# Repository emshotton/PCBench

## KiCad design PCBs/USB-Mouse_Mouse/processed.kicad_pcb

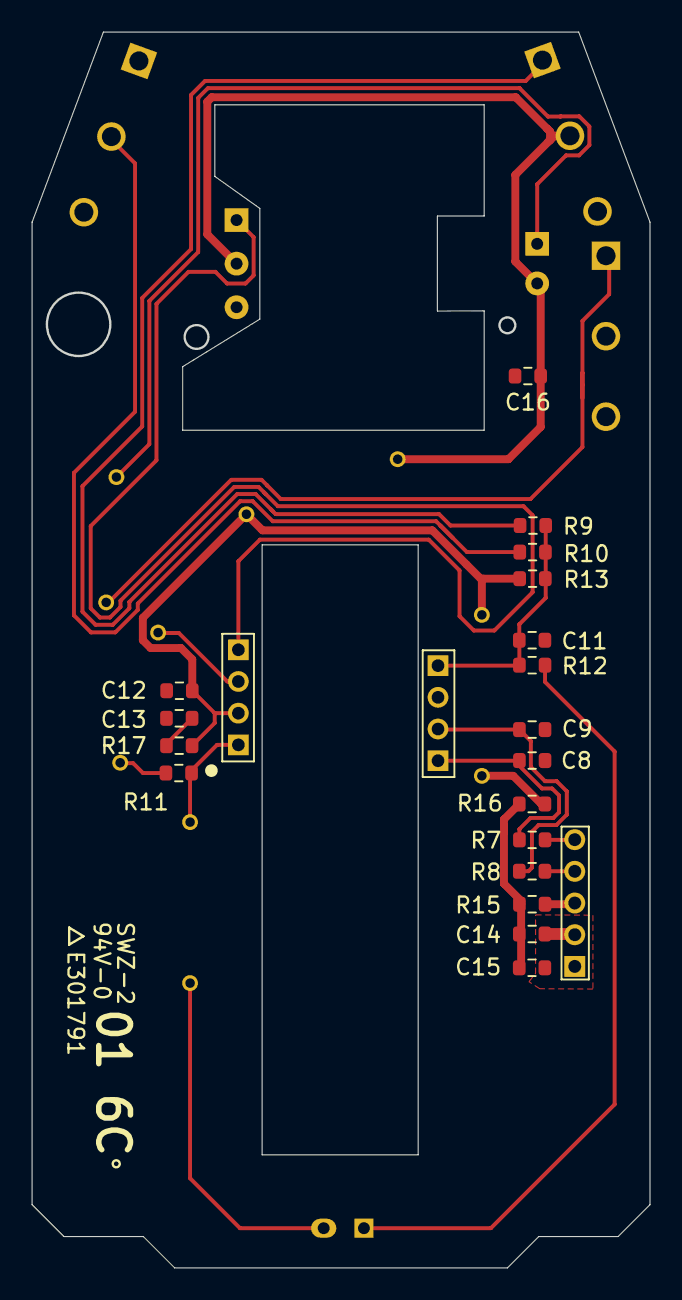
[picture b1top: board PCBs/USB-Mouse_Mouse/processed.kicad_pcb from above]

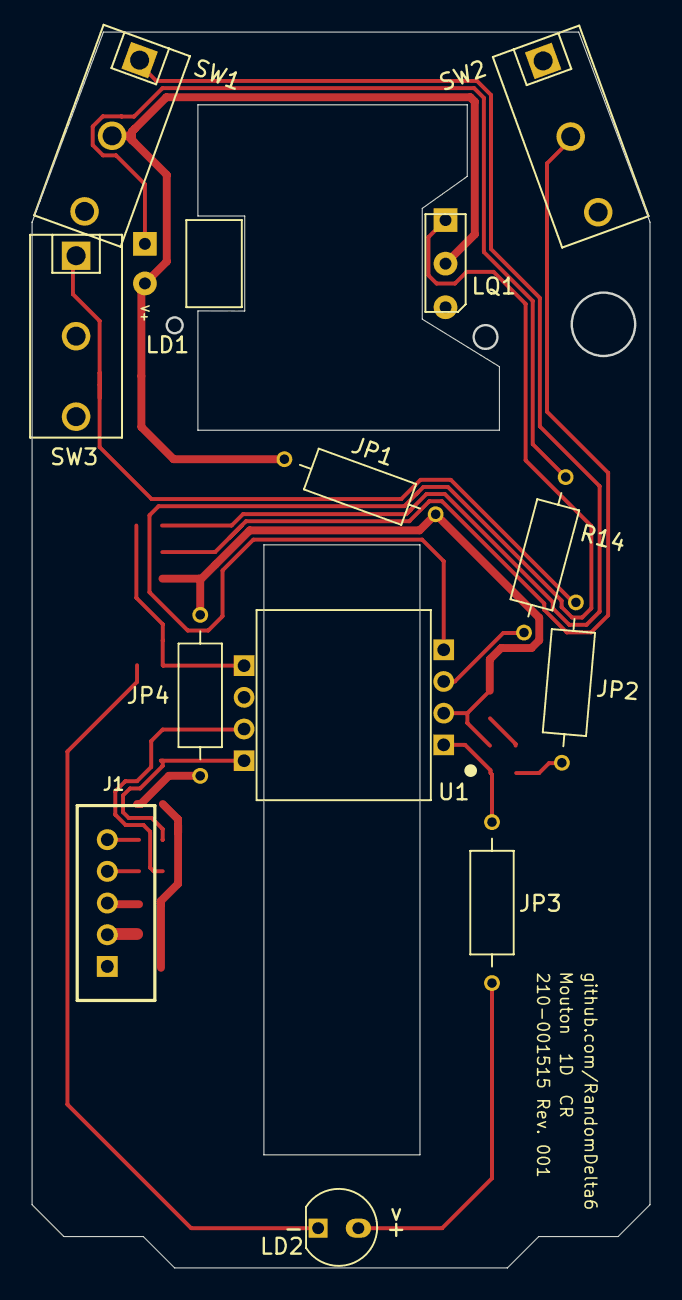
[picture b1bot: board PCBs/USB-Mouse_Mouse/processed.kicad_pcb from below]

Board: 2 copper layers, 39.0 x 78.0 mm, 31 parts (13 on the bottom side), 22 nets.

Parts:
C8, C9: C 0.01uF; R_0603_1608_Logi
C11, C13, C16: C NC; R_0603_1608_Logi
C12, C15: C 0.1uF; R_0603_1608_Logi
C14: C 4.7uF; R_0603_1608_Logi
J1: Conn_01x05_Male; JST_Conn
JP1, JP2, JP3, JP4: R; JP_Axial_DIN0207_L6.3mm_D2.5mm_P10.16mm_Horizontal
LD1: Rotary illumintion; Rot_LED
LD2: Sensor illumination; LED_Sensor
LQ1: EL; LQ1
R7, R8: R 270; R_0603_1608_Logi
R9, R10, R11: R 303; R_0603_1608_Logi
R12: R 330; R_0603_1608_Logi
R13: R 105; R_0603_1608_Logi
R14: R 1500ohm ± 5%; JP_Axial_DIN0207_L6.3mm_D2.5mm_P10.16mm_Horizontal
R15: R 1R0; R_0603_1608_Logi
R16: R 000; R_0603_1608_Logi
R17: R NC; R_0603_1608_Logi
SW1: Left click; SPDT_Switch
SW2: Right Click; SPDT_Switch
SW3: Middle click; SPDT_Switch
U1: Optical_Sensor; Sensor

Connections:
D+: C9.1, R8.2, U1.7
D-: C8.1, R7.1, U1.8
GNDREF: C8.2, C9.2, C11.1, C12.1, C13.1, C14.1, C15.2, C16.2, J1.1, J1.2, LQ1.3, SW2.1, SW3.2, U1.6
unnamed: C13.2, R17.1
unnamed: C14.2, C15.1, R15.1, R16.2
unnamed: J1.4, R8.1
unnamed: J1.5, R7.2
unnamed: JP2.1, SW3.1
unnamed: JP2.2, R11.2
unnamed: JP3.1, LD2.1
unnamed: JP4.1, R16.1
unnamed: LD1.1, R14.1
unnamed: LD2.2, R12.2
unnamed: R9.2, SW1.1
unnamed: R10.1, SW2.2
Pin_1: JP3.2, R11.1, U1.1
Pin_2: C12.2, JP1.2, JP4.2, R13.2, R17.2, U1.2
Pin_2J: C16.1, JP1.1, LD1.2, LQ1.2, SW1.2
Pin_3: R14.2, U1.3
Pin_4: LQ1.1, U1.4
Pin_5: C11.2, R9.1, R10.2, R12.1, R13.1, U1.5
VCC: J1.3, R15.2

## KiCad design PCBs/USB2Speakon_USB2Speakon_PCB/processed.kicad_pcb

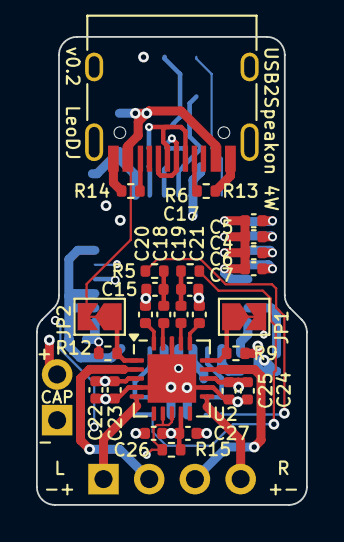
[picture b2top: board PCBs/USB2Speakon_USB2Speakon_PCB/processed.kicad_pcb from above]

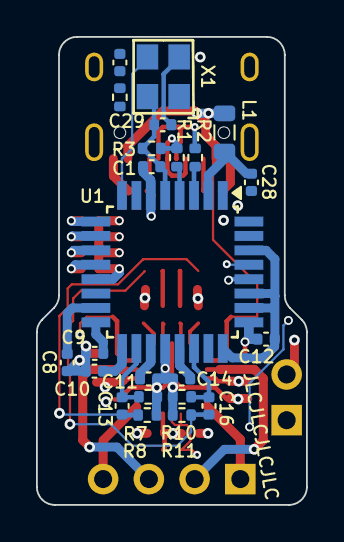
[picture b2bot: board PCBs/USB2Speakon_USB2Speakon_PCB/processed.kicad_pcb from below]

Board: 4 copper layers, 15.0 x 26.0 mm, 52 parts (23 on the bottom side), 36 nets.

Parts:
C1, C8, C11, C12, C14, C28: 1u; C_0402_1005Metric
C2: DNP; C_0402_1005Metric
C4, C5: 100p; C_0402_1005Metric
C6, C10: 3u3; C_0402_1005Metric
C7, C9, C23, C25, C27, C29: 100n; C_0402_1005Metric
C13, C16, C22, C24, C26: 10u; C_0402_1005Metric
C15, C17: 47n; C_0402_1005Metric
C18, C19, C20, C21: 470n; C_0402_1005Metric
J1: USB_C_Receptacle_USB2.0_16P; USB_C_Receptacle_HRO_TYPE-C-31-M-12
J2: Conn_01x04; PinHeader_1x04_P2.54mm_Vertical
J3: Ext_Cap; PinSocket_1x02_P2.54mm_Vertical
JP1: G0; SolderJumper-2_P1.3mm_Open_TrianglePad1.0x1.5mm
JP2: G1; SolderJumper-2_P1.3mm_Open_TrianglePad1.0x1.5mm
L1: 1uH / <0.6Ω; L_0805_2012Metric
R1, R2: 22; R_0402_1005Metric
R3: 1k5; R_0402_1005Metric
R4: DNP; R_0402_1005Metric
R5, R6: 100; R_0402_1005Metric
R7, R8, R9, R10, R11, R12, R15: 33k; R_0402_1005Metric
R13, R14: 5k1; R_0402_1005Metric
U1: PCM2912A; TQFP-32_7x7mm_P0.8mm
U2: TPA2012D2RTJR; QFN-20-1EP_4x4mm_P0.5mm_EP2.7x2.7mm
X1: 6MHz XO; OSC-SMD_4P-L3.2-W2.5-BL

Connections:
+3V3: C1.2, C29.2, R3.2, U1.5 (VDD), X1.4 (V+)
GND: C1.1, C4.1, C5.1, C6.1, C7.1, C8.1, C9.1, C10.1, C11.1, C12.1, C14.1, C15.2, C17.2, C20.2, C21.2, C22.2, C23.2, C24.2, C25.2, C26.2, C27.2, C28.2, C29.1, J1.A1 (GND), J1.A12 (GND), J1.B1 (GND), J1.B12 (GND), J1.S1 (SHIELD), J3.1, R7.2, R8.2, R9.2, R10.1, R11.1, R12.2, R13.2, R14.2, U1.1 (BGND), U1.6 (DGND), U1.13 (AGND), U1.20 (HGND), U1.23 (MAMP), U1.25 (PGND), U1.28 (TEST0), U2.4 (PGND), U2.12 (PGND), U2.18 (AGND), U2.21 (EP), X1.2 (GND)
LINE_L: C13.1, R5.1, R8.1
LINE_R: C16.1, R6.1, R11.2
unnamed: C15.1, C18.1, R5.2
unnamed: C17.1, C19.1, R6.2
unnamed: J1.A5 (CC1), R13.1
unnamed: J1.B5 (CC2), R14.1
unnamed: J1.A6 (D+), J1.B6 (D+), R1.1, R3.1
unnamed: J1.A7 (D-), J1.B7 (D-), R2.2
unnamed: J2.1, U2.5 (OUTL-)
unnamed: J2.2, U2.2 (OUTL+)
unnamed: J2.3, U2.14 (OUTR+)
unnamed: J2.4, U2.11 (OUTR-)
unnamed: R1.2, U1.4 (D+)
unnamed: R2.1, U1.3 (D-)
unnamed: C5.2, U1.9 (FL)
unnamed: C4.2, U1.10 (FR)
unnamed: C10.2, U1.17 (MBIAS)
unnamed: C28.1, L1.2, U1.2 (VBUS)
unnamed: C8.2, U1.15 (VCCCA)
unnamed: C11.2, U1.19 (VCCL)
unnamed: C14.2, U1.21 (VCCR)
unnamed: C6.2, U1.11 (VCOM1)
unnamed: C7.2, U1.12 (VCOM2)
unnamed: C9.2, U1.16 (VIN)
unnamed: C13.2, R7.1, U1.18 (VOUTL)
unnamed: C16.2, R10.2, U1.22 (VOUTR)
unnamed: U1.8 (XTI), X1.3 (OUT)
unnamed: C20.1, U2.20 (INL+)
unnamed: C18.2, U2.19 (INL-)
unnamed: C21.1, U2.16 (INR+)
unnamed: C19.2, U2.17 (INR-)
VBUS: C22.1, C23.1, C24.1, C25.1, C26.1, C27.1, J1.A4 (VBUS), J1.A9 (VBUS), J1.B4 (VBUS), J1.B9 (VBUS), J3.2, JP1.1 (A), JP1.2 (B), JP2.1 (A), JP2.2 (B), L1.1, R9.1, R12.1, R15.1, U2.1 (G1), U2.3 (PVDD), U2.9 (AVDD), U2.13 (PVDD), U2.15 (G0)
VCCP: C12.2, U1.24 (POWER), U1.26 (VCCP), U1.27 (TEST1), U1.30 (MMUTE)
~SSPND: R15.2, U1.29 (~SSPND), U2.7 (SDL), U2.8 (SDR)

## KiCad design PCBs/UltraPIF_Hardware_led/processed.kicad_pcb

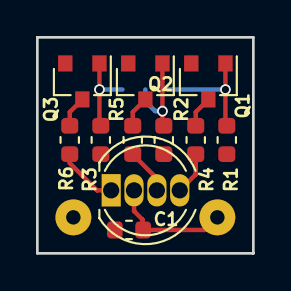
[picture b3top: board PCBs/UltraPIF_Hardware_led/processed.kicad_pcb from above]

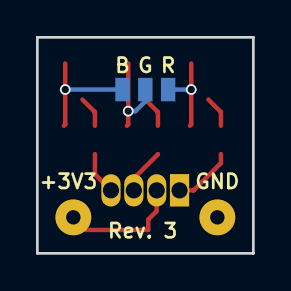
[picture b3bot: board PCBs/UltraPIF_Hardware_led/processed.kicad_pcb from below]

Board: 2 copper layers, 12.0 x 12.0 mm, 16 parts (3 on the bottom side), 11 nets.

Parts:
C1: 1u; C_0603_1608Metric
J1, J2, J3: CONN_01X01; SolderWirePad_1x01_SMD_0.8x1.3mm
J4, J5: CONN_01X01; SolderWirePad_1x01_Drill0.8mm
LD1: LED_RAGB; LED_D5.0mm-4_RGB
Q1, Q2, Q3: Q_NMOS_GSD; SOT-23
R1, R2, R3: 10k; R_0603_1608Metric
R4: 27; R_0603_1608Metric
R5: 56; R_0603_1608Metric
R6: 82; R_0603_1608Metric

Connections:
+3V3: C1.1, J4.1, LD1.2
/BLUE: J1.1, Q1.1, R1.1
/BLUE_D: Q1.3, R4.2
/BLUE_K: LD1.4, R4.1
/GREEN: J2.1, Q2.1, R2.1
/GREEN_D: Q2.3, R5.2
/GREEN_K: LD1.3, R5.1
/RED: J3.1, Q3.1, R3.1
/RED_D: Q3.3, R6.2
/RED_K: LD1.1, R6.1
GND: C1.2, J5.1, Q1.2, Q2.2, Q3.2, R1.2, R2.2, R3.2

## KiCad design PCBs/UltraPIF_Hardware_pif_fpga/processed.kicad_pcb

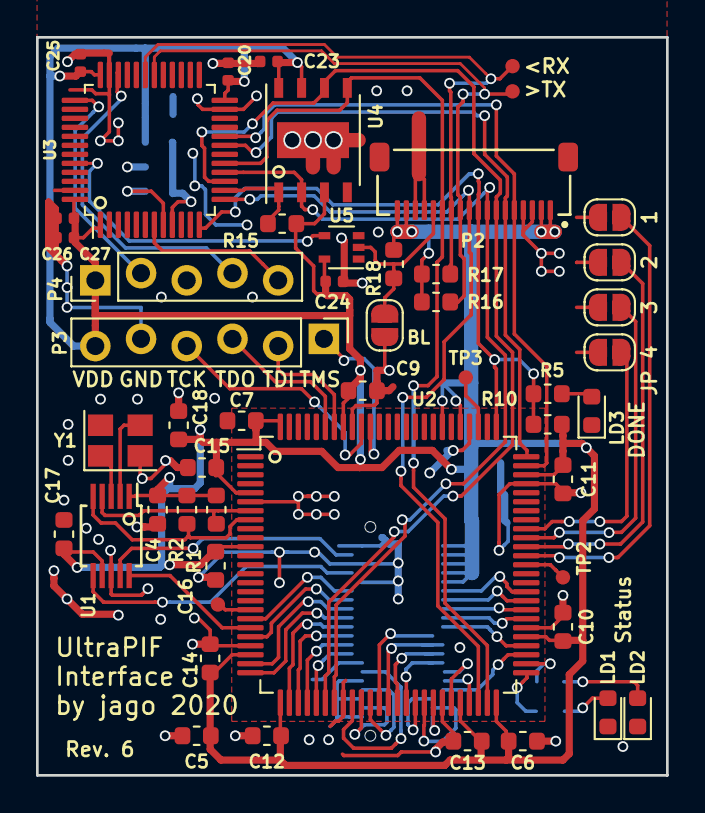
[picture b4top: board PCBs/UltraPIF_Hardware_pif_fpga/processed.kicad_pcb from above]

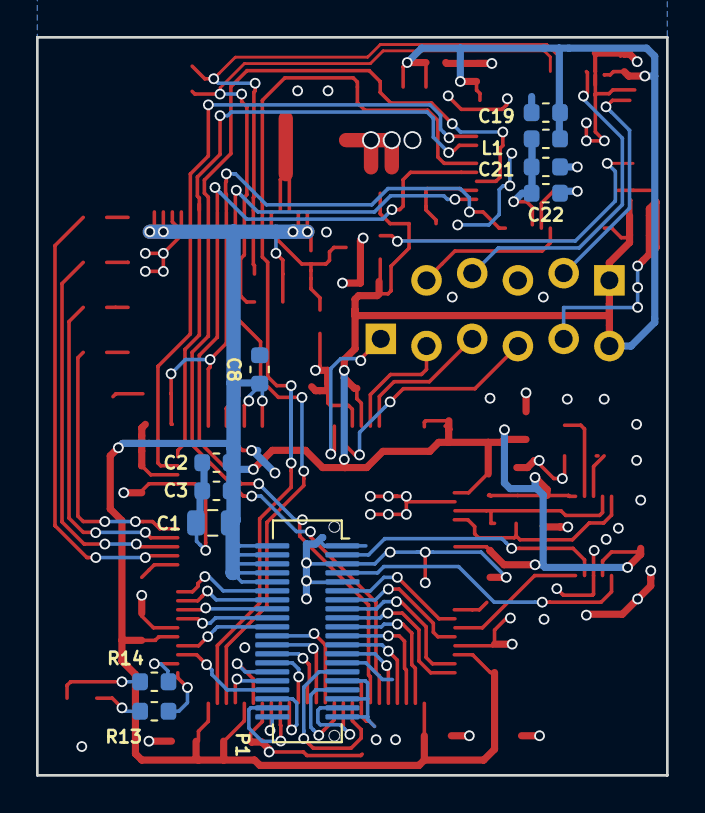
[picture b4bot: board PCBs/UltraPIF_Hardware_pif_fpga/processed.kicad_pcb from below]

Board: 2 copper layers, 35.0 x 41.0 mm, 61 parts (11 on the bottom side), 67 nets.

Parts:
C1: 10u; C_0805_2012Metric
C2, C21: 1u; C_0603_1608Metric
C3: 10n; C_0603_1608Metric
C4, C6, C7, C8, C9, C10, C11, C12, C13, C14, C15, C16, C17, C22: 100n; C_0603_1608Metric
C5, C18, C19: 4u7; C_0603_1608Metric
C20, C23, C24, C25, C26, C27: 100n; C_0402_1005Metric
JP1, JP2, JP3, JP4, JP5: Jumper_NO_Small; SolderJumper-2_P1.3mm_Open_RoundedPad1.0x1.5mm
L1: Ferrite; L_0603_1608Metric
LD1, LD2, LD3: LED_Small; LED_0603_1608Metric
P1: CONN_02X20; Hirose_DF12A-40DS-0.5V_2x20_P0.50mm_Vertical
P2: CONN_01X18; Molex_BackFlip_18x0.5mm
P3: CONN_01X06; PinHeader_1x06_P2.54mm_NoSolder
P4: CONN_01X05; PinHeader_1x05_P2.54mm_NoSolder
R1, R2, R15, R16, R17, R18: 10k; R_0603_1608Metric
R5, R10: 220; R_0603_1608Metric
R13, R14: 330; R_0603_1608Metric
TP1, TP2, TP3: TEST_1P; TP_0.8mm
TP4, TP5: TestPoint; TP_0.8mm
U1: Si5351A; MSOP-10_3x3mm_P0.5mm
U2: LCMXO2-2000HC; TQFP-100_14x14mm_P0.5mm
U3: STM32F070CBT6; LQFP-48_7x7mm_P0.5mm
U4: W25Q128JVPIQ; DFN-8-1EP_6x5mm_P1.27mm_EP2x2mm
U5: 74LVC1G14; SOT-353_SC-70-5
Y1: 25 MHz; Crystal_SMD_3225-4Pin_3.2x2.5mm

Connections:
+3V3: C1.1, C2.1, C3.1, C4.1, C5.1, C6.1, C7.1, C8.1, C9.1, C10.1, C11.1, C12.1, C13.1, C14.1, C15.1, C16.1, C17.1, C18.1, C19.1, C20.1, C23.1, C24.1, C25.1, C26.1, C27.1, L1.1, P1.1, P1.3, P1.5, P1.7, P1.9, P2.1, P2.2, P2.17, P2.18, P3.6, P4.1, R1.1, R2.1, R10.1, R15.1, R16.1, R17.1, R18.1, U1.1, U1.7, U2.5, U2.11, U2.23, U2.26, U2.46, U2.50, U2.55, U2.73, U2.80, U2.82, U2.93, U2.100, U3.1, U3.24, U3.36, U3.48, U4.3, U4.7, U4.8, U5.5
/ADR_PIF: P1.34, U2.36
/BLUE: P1.39, U2.43
/BOOT: JP5.1, P2.14, R18.2, U5.2
/CIC_DCLK: P1.16, U2.24
/CIC_DIO: P1.20, U2.27
/CLK_CIC_EEP: P1.12, U2.19
/CLK_FSC: P1.8, U1.6
/CLK_FSO_5: P1.4, U1.9
/CLK_INT: U1.10, U2.20
/CLK_PIF: P1.30, U2.34
/COLD_RESET: P1.22, U2.28
/DAT_PIF: P1.38, U2.35
/EEP_DAT: P1.15, U2.58
/EN_PIF: P1.26, U2.30
/FPGA/JP1: JP1.1, U2.64
/FPGA/JP2: JP2.1, U2.65
/FPGA/JP3: JP3.1, U2.66
/FPGA/JP4: JP4.1, U2.67
/FPGA/LED1: R13.2, U2.51
/FPGA/LED2: R14.2, U2.52
/FPGA/TCK: P3.4, U2.91
/FPGA/TDI: P3.2, U2.94
/FPGA/TDO: P3.3, U2.95
/FPGA/TEST1: TP1.1, U2.18
/FPGA/TEST2: TP2.1, U2.63
/FPGA/TEST3: TP3.1, U2.78
/FPGA/TMS: P3.1, U2.90
/FPGA_CS: P2.6, U2.75, U3.19
/FPGA_DONE: P2.9, R5.1, R10.2, U2.76, U3.12
/FPGA_MISO: P2.8, U2.32, U3.16, U4.2
/FPGA_MOSI: P2.13, U2.49, U3.17, U4.5
/FPGA_SCK: P2.7, U2.31, U3.15, U4.6
/GREEN: P1.37, U2.42
/INT_CPU: P1.13, U2.59
/IRQ: P2.5, U2.74, U3.20
/MCU/BOOT0: U3.44, U5.4
/MCU/FLASH_CS: R15.2, U3.14, U4.1
/MCU/NRST: P4.5, U3.7
/MCU/SWCLK: P4.2, U3.37
/MCU/SWDIO: P4.4, U3.34
/MCU/VDDA: C21.1, C22.1, L1.2, U3.9
/NMI_CPU: P1.24, U2.29
/OUTPUT_RST: P1.18, U2.25
/P1_AUX: P1.33, U2.53
/P1_DAT_IN: P1.29, U2.45
/P1_DAT_OUT: P1.31, U2.47
/P2_DAT_IN: P1.25, U2.39
/P2_DAT_OUT: P1.27, U2.40
/P3_DAT_IN: P1.21, U2.37
/P3_DAT_OUT: P1.23, U2.38
/P4_DAT_IN: P1.17, U2.57
/P4_DAT_OUT: P1.19, U2.54
/RC_POR: P1.14, U2.21
/RED: P1.35, U2.41
/RESET_BTN: P1.11, U2.60
/SCL: R1.2, U1.4, U2.7
/SDA: R2.2, U1.5, U2.8
/UART_RX: P2.12, R17.2, TP4.1, U3.31
/UART_TX: P2.11, R16.2, TP5.1, U3.30
/UFM_SN: P2.10, U2.48, U3.13
GND: C1.2, C2.2, C3.2, C4.2, C5.2, C6.2, C7.2, C8.2, C9.2, C10.2, C11.2, C12.2, C13.2, C14.2, C15.2, C16.2, C17.2, C18.2, C19.2, C20.2, C21.2, C22.2, C23.2, C24.2, C25.2, C26.2, C27.2, JP1.2, JP2.2, JP3.2, JP4.2, JP5.2, LD1.1, LD2.1, LD3.1, P1.2, P1.6, P1.10, P1.28, P1.32, P1.36, P1.40, P2.3, P2.4, P2.15, P2.16, P3.5, P4.3, U1.8, U2.6, U2.22, U2.33, U2.44, U2.56, U2.72, U2.79, U2.92, U3.8, U3.23, U3.35, U3.47, U4.4, U4.9, U5.3, Y1.2, Y1.4
unnamed: LD1.2, R13.1
unnamed: LD2.2, R14.1
unnamed: LD3.2, R5.2
unnamed: U1.2, Y1.3
unnamed: U1.3, Y1.1

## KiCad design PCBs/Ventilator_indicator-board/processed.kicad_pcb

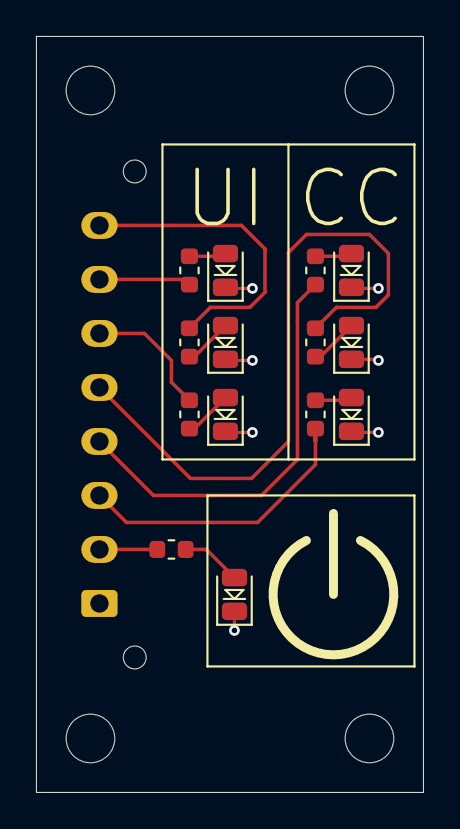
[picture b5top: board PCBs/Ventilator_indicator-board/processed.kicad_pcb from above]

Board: 4 copper layers, 21.5 x 42.0 mm, 19 parts (1 on the bottom side), 15 nets.

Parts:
D1, D2, D5: Green; LED_0805_2012Metric
D3, D6: Yellow; LED_0805_2012Metric
D4, D7: Red; LED_0805_2012Metric
H1, H2, H3, H4: M2.5; MountingHole_2.7mm
J1: Cable to from main board; Molex_Micro-Fit_3.0_43650-0815_1x08_P3.00mm_Vertical
R1, R2, R3, R4, R5, R6, R7: 1k; R_0603_1608Metric

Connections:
+5V: J1.2, R1.1
/CC-LED-G: J1.3, R2.1
/CC-LED-R: J1.4, R4.1
/CC-LED-Y: J1.5, R3.1
/UI-LED-G: J1.6, R5.1
/UI-LED-R: J1.7, R7.1
/UI-LED-Y: J1.8, R6.1
GND: D1.1, D2.1, D3.1, D4.1, D5.1, D6.1, D7.1, J1.1
unnamed: D1.2, R1.2
unnamed: D2.2, R2.2
unnamed: D3.2, R3.2
unnamed: D4.2, R4.2
unnamed: D5.2, R5.2
unnamed: D6.2, R6.2
unnamed: D7.2, R7.2

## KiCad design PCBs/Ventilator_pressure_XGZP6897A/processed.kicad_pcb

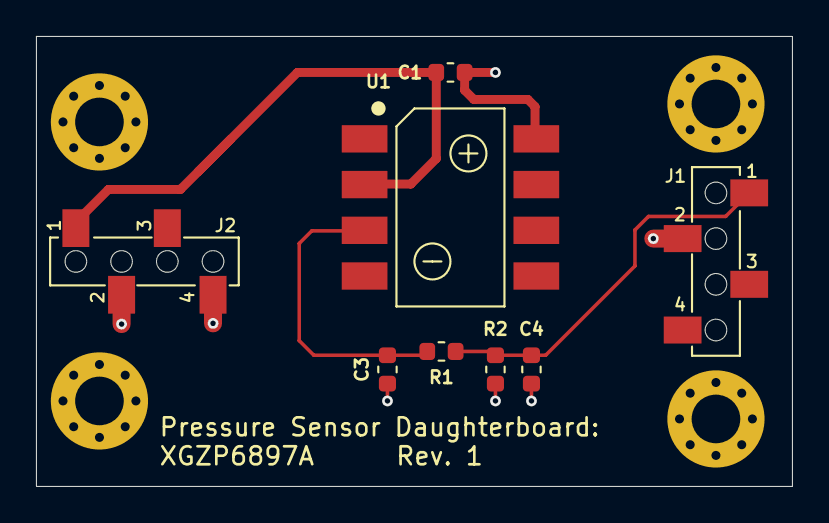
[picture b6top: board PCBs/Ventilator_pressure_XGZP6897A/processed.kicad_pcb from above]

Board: 2 copper layers, 42.0 x 25.0 mm, 12 parts (0 on the bottom side), 4 nets.

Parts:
C1, C4: 1uF; C_0603_1608Metric
C3: 470pF; C_0603_1608Metric
H1, H2, H3, H4: M2.5; MountingHole_2.7mm_M2.5_Pad_Via
J1, J2: Main board connections (bottom entry); PinSocket_1x04_P2.54mm_Vertical_SMD_TE_1241152-4
R1: 2.4K; R_0603_1608Metric
R2: 4.7K; R_0603_1608Metric
U1: XGZP6897A005KPD; XGZP6897A

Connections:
+5V_Sns: C1.2, J2.1, U1.2
GND: C1.1, C3.1, C4.1, J1.2, J2.2, J2.4, R2.1, U1.8
unnamed: C3.2, R1.2, U1.3
unnamed: C4.2, J1.1, R1.1, R2.2
